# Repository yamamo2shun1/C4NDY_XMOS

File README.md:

# C4NDY_XMOS

## How to build & Run
```
> cd xC/app_XXXX
> cmake -G "Unix Makefiles" -B build
> cd build
> xmake
> xrun --io ../bin/XXXX.xe
```

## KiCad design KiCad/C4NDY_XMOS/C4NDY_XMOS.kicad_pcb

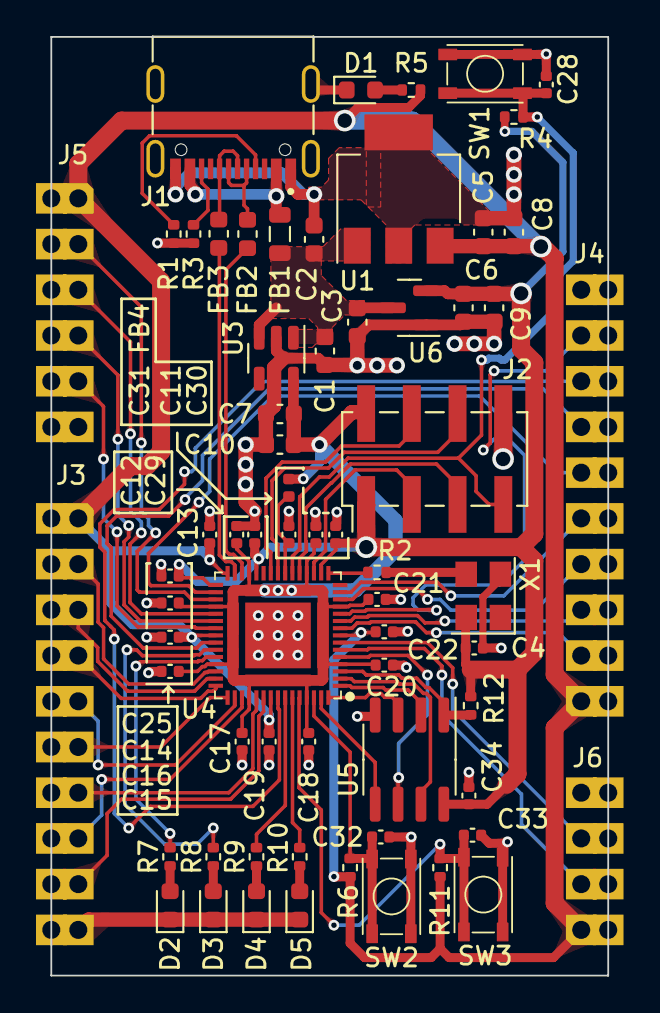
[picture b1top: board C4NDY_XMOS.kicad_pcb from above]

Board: 2 copper layers, 30.9 x 52.2 mm, 66 parts (0 on the bottom side), 59 nets.

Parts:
C1, C3, C6, C7, C9, C10: 1uF; C_0603_1608Metric
C2, C5, C8: 4.7uF; C_0603_1608Metric
C4, C11, C12, C13, C14, C15, C16, C17, C18, C19, C20, C21, C22, C25, C28, C29, C30, C32, C33, C34: 100nF; C_0402_1005Metric
C31: 1uF; C_0402_1005Metric
D1, D2, D3, D4, D5: LED; LED_0603_1608Metric
FB1: BLM21PG221SN1; L_0805_2012Metric
FB2, FB3: BLM18BB121SN1; L_0603_1608Metric
FB4: BLM15PX601SN1D; L_0402_1005Metric
J1: UB1611-HGN; Gangyuan_UB1611-HGN
J2: JTAG; PinHeader_2x04_P2.54mm_Vertical_SMD
J3, J4: Conn_01x10; PinHeader_2x10_P2.54mm
J5: Conn_01x06; PinHeader_2x06_P2.54mm
J6: Conn_01x04; PinHeader_2x04_P2.54mm
R1, R3: 5.1k; R_0402_1005Metric
R2: 33; R_0402_1005Metric
R4, R6, R11: 10k; R_0402_1005Metric
R5, R7, R8, R9, R10: 1k; R_0402_1005Metric
R12: 4.7k; R_0402_1005Metric
SW1, SW2, SW3: SKRPABE010
U1: AP7361EA-33E-13; SOT-223-3_TabPin2
U3: AP7343Q-09W5-7; SOT-23-5
U4: XU316-1024-QF60B-C32; XU316-1024-QF60
U5: AT25FF321A-SSHN-T; SOIC-8_3.9x4.9mm_P1.27mm
U6: AP2127N-1.8TRG1; SOT-23
X1: SG-210STF 24.0000ML0; Oscillator_SMD_SeikoEpson_SG8002CE-4Pin_3.2x2.5mm

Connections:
+1V8: C4.2, C6.1, C9.1, C25.1, C29.1, C30.1, C34.1, J2.1, R4.1, R12.1, U4.17 (VDDIOB18), U4.26 (VDDIOB18), U4.31 (USB_VDD18), U5.8 (VDD), U6.2 (VO), X1.4 (Vcc)
+3V3: C5.1, C8.1, C13.1, C16.1, C19.1, C22.1, J3.1, J4.1, J5.1, J6.1, R5.1, R6.1, R11.1, U1.3 (VO), U4.8 (VDDIOL), U4.30 (USB_VDD33), U4.38 (VDDIOR), U4.52 (VDDIOT)
/1A0: J4.2, U4.9 (X1D00)
/1B0: J4.3, U4.10 (X1D01)
/1C0: J4.4, U4.13 (X1D10)
/1D0: J4.5, U4.14 (X1D11)
/1F0: J4.6, U4.32 (X1D13)
/1G0: J4.7, U4.39 (X1D22)
/1K0: J4.8, U4.53 (X1D34)
/4A3: J4.9, U4.11 (X1D09)
/4D0: J5.2, U4.33 (X1D16)
/4D1: J5.3, U4.35 (X1D17)
/4D2: J5.4, U4.36 (X1D18)
/4D3: J5.5, U4.37 (X1D19)
/8D0: J3.2, U4.43 (X0D36)
/8D1: J3.3, U4.44 (X0D37)
/8D2: J3.4, U4.45 (X0D38)
/8D3: J3.5, U4.47 (X0D39)
/8D4: J3.6, U4.46 (X0D40)
/8D5: J3.7, U4.50 (X0D41)
/8D6: J3.8, U4.48 (X0D42)
/8D7: J3.9, U4.51 (X0D43)
/DN: FB2.1, J1.A7 (DN1), J1.B7 (DN2)
/DP: FB3.1, J1.A6 (DP1), J1.B6 (DP2)
/LED0: R7.1, U4.41 (X0D35)
/LED1: R8.1, U4.40 (X0D29)
/LED2: R9.1, U4.54 (X0D30)
/LED3: R10.1, U4.55 (X0D31)
/OSC: R2.2, U4.16 (XIN)
/QSPI_CLK: U4.5 (X0D10), U5.6 (CLK)
/QSPI_IO0: U4.59 (X0D04), U5.5 (SI/SIO0)
/QSPI_IO1: U4.1 (X0D05), U5.2 (SO/SIO1)
/QSPI_IO2: U4.60 (X0D06), U5.3 (SIO2)
/QSPI_IO3: U4.2 (X0D07), U5.7 (SIO3)
/QSPI_NCS: R12.2, U4.3 (X0D01), U5.1 (CE)
/RST_N: C28.1, J2.7, R4.2, SW1.3 (K), SW1.4 (A), U4.21 (RST_N)
/SW0: C32.1, R6.2, SW2.3 (K), SW2.4 (A), U4.58 (X0D33)
/SW1: C33.1, R11.2, SW3.3 (K), SW3.4 (A), U4.56 (X0D32)
/TCK: J2.4, U4.24 (TCK)
/TDI: J2.3, U4.18 (TDI)
/TDO: J2.5, U4.20 (TDO)
/TMS: J2.6, U4.23 (TMS)
/USB_DM: FB2.2, U4.28 (USB_DM)
/USB_DP: FB3.2, U4.29 (USB_DP)
/X0D00: J6.2, U4.6 (X0D00)
/X0D11: J6.3, U4.7 (X0D11)
GND: C1.2, C2.2, C3.2, C4.1, C5.2, C6.2, C7.2, C8.2, C9.2, C10.2, C11.2, C12.2, C13.2, C14.2, C15.2, C16.2, C17.2, C18.2, C19.2, C20.2, C21.2, C22.2, C25.2, C28.2, C29.2, C30.2, C31.2, C32.2, C33.2, C34.2, D1.1 (K), D2.1 (K), D3.1 (K), D4.1 (K), D5.1 (K), J1.A1_B12 (GND), J1.B1_A12 (GND), J1.S1 (SHIELD), J1.S2 (SHIELD), J1.S3 (SHIELD), J1.S4 (SHIELD), J2.8, J3.10, J4.10, J5.6, J6.4, R1.2, R3.2, SW1.1, SW1.2, SW2.1, SW2.2, SW3.1, SW3.2, U1.2 (GND), U3.2 (GND), U4.65 (VSS), U5.4 (VSS), U6.1 (GND), X1.2 (GND)
unnamed: D1.2 (A), R5.2
unnamed: D2.2 (A), R7.2
unnamed: D3.2 (A), R8.2
unnamed: D4.2 (A), R9.2
unnamed: D5.2 (A), R10.2
unnamed: FB1.1, J1.A4_B9 (VBUS), J1.B4_A9 (VBUS)
unnamed: J1.A5 (CC1), R1.1
unnamed: J1.B5 (CC2), R3.1
unnamed: C31.1, FB4.1, U4.22 (PLL_AVDD)
unnamed: R2.1, X1.3 (OUT)
VBUS: C1.1, C2.1, C3.1, FB1.2, U1.1 (VI), U3.1 (VIN), U3.3 (EN), U6.3 (VI)
VCC: C7.1, C10.1, C11.1, C12.1, C14.1, C15.1, C17.1, C18.1, C20.1, C21.1, FB4.2, J2.2, U3.5 (VOUT), U4.4 (VDD), U4.12 (VDD), U4.19 (VDD), U4.27 (VDD), U4.34 (VDD), U4.42 (VDD), U4.49 (VDD), U4.57 (VDD), U4.61 (VDD), U4.62 (VDD), U4.63 (VDD), U4.64 (VDD)

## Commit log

2024-02-05 Add ignore file.
2024-02-05 Add KiCad project files.
2024-02-05 Add XN file.
2024-02-06 Add hello world example.
2024-02-06 Ignore bin and build folder.
2024-02-06 Add schematic pdf.
2024-02-06 Ignore all bin and build directory.
2024-02-06 Add led blink example.
2024-02-06 Removed submodule lib_i2c
2024-02-06 Removed submodule lib_xassert
2024-02-06 Ignore lib_XXX directory.
2024-02-06 Add I2C read example.
2024-02-07 Move directory.
2024-02-07 Add XN file for C4NDY XMOS board.
2024-02-07 Add boot from flash example.
